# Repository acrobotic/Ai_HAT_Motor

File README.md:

## Ai\_HAT\_Motor

PCB design files (EAGLE) for a Raspberry Pi A+/B+/2/3 HAT carrying a motor
and servo driver ICs (DRV8835 and PCA9685, respectively), as well as a 4-Channel 
ADC (ADS1115). 

## Description

Visit our online shop at:

   * https://acrobotic.com/

Designed by ACROBOTIC Industries.  Please consider buying products from us to 
help fund future Open-Source projects like this! We’ll always put our best 
effort in every project, and release all our design files and code for you to 
use. 

## License

Released under the Creative Commons Attribution, Share-Alike license. Please 
check LICENSE.txt for more information. All text above must be included in any 
redistribution.

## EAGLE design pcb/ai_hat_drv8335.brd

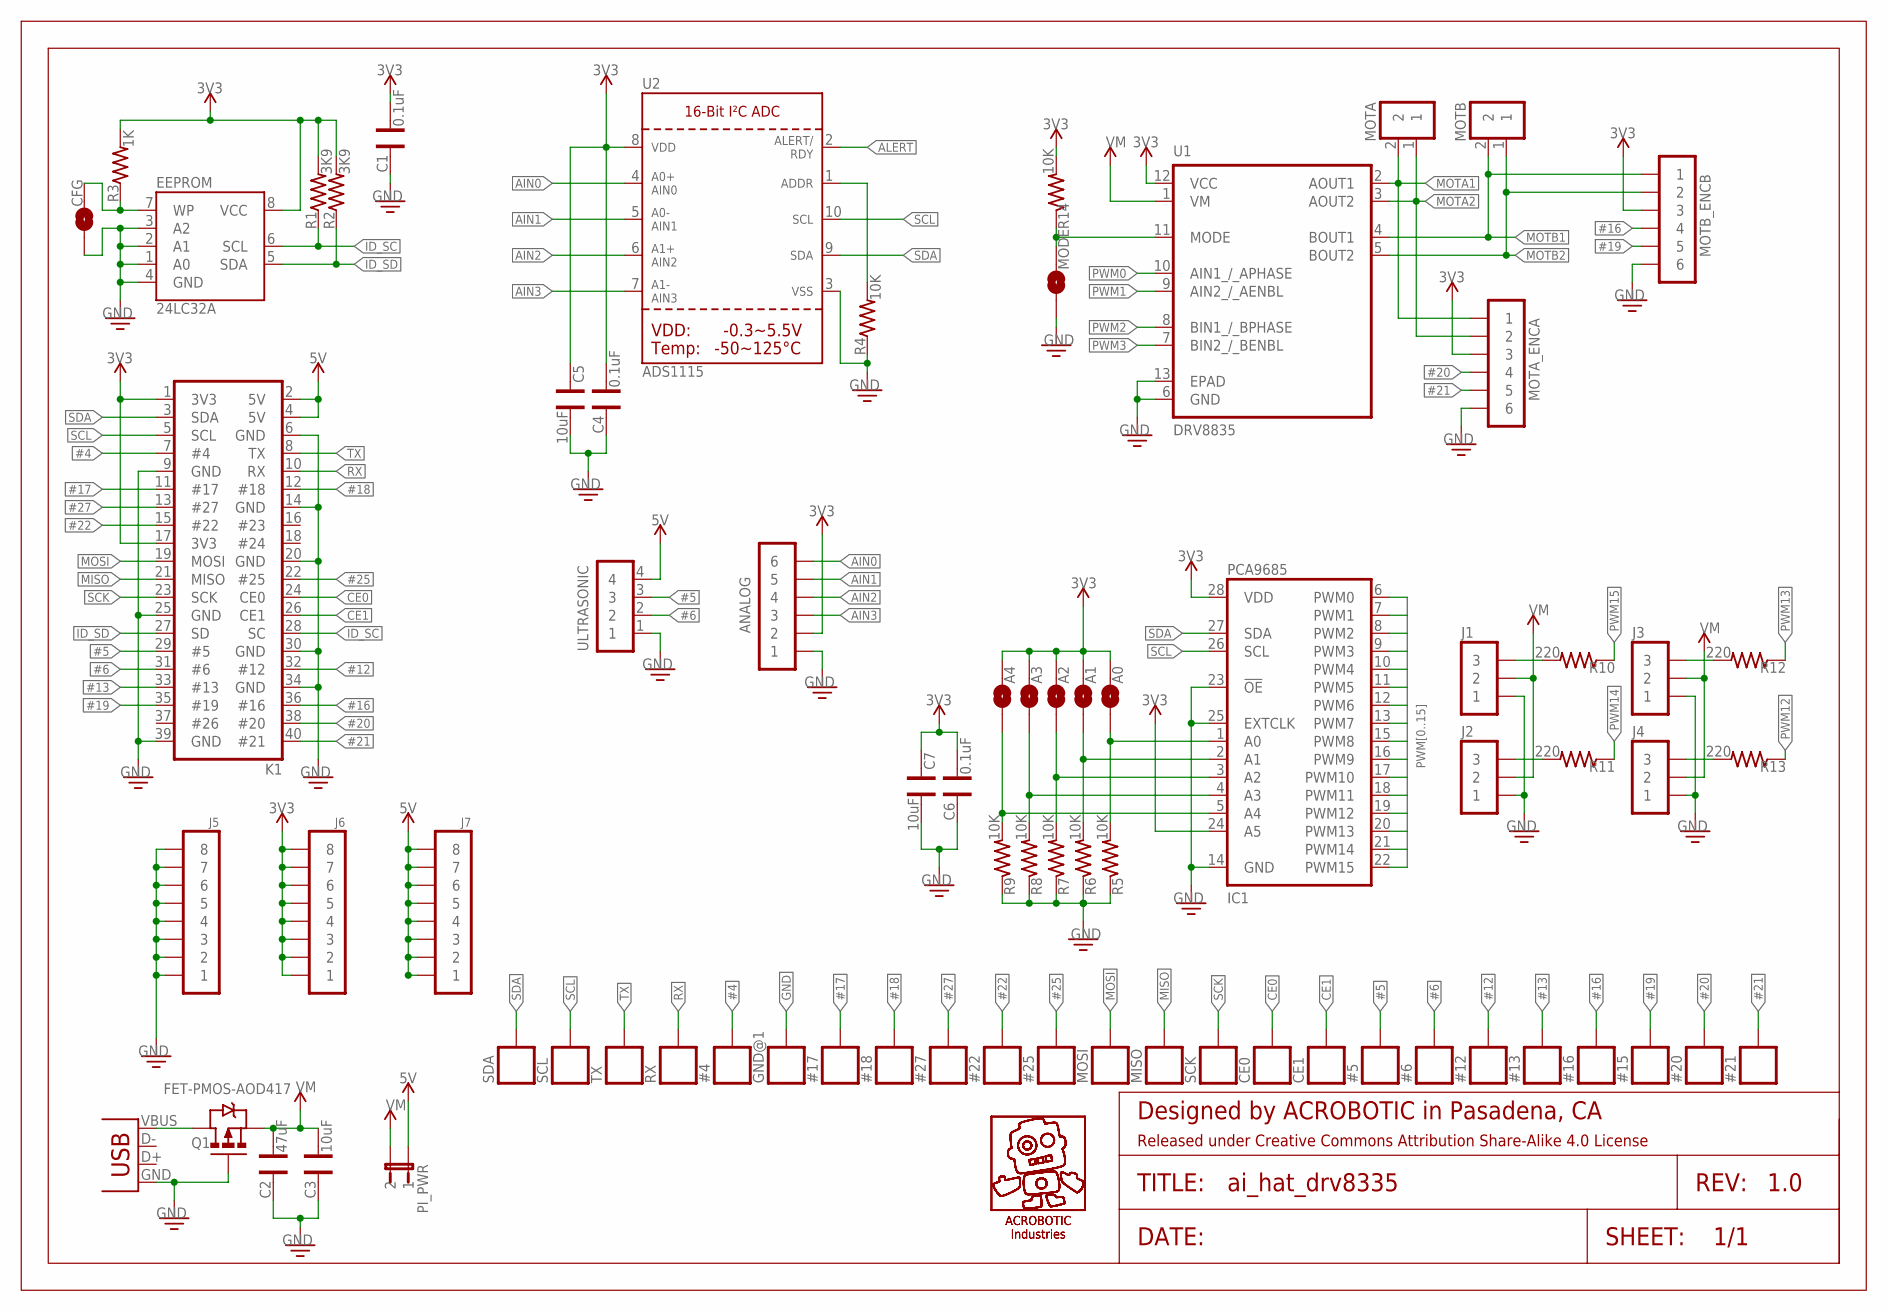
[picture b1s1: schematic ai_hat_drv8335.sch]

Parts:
#4, #5, #6, #12, #13, #15, #16, #17, #18, #20, #21, #22, #25, #27: 1X01-SM
A0, A1, A2, A3, A4: 1X02-SJ-NO
ANALOG: 1X06
C1: 0.1uF; CAP-0603
C2: 47uF; CAP-0603
C3: 10uF; CAP-0603
C4, C6: 0.1uF; CAP-0402
C5, C7: 10uF; CAP-0402
CE0, CE1: 1X01-SM
CFG: 1X02-SJ-NO
EEPROM: 24LC32A; SO08-EIAJ
FRAME1: FRAME-LETTER; CREATIVE-COMMONS
GND@1: 1X01-SM
IC1: PCA9685; TSSOP28
J1, J2, J3, J4: 1X03
J5, J6, J7: 1X08
K1: 2X20-RPI-ALT
MISO: 1X01-SM
MODE: 1X02-SJ-NO
MOSI: 1X01-SM
MOTA: 1X02ST; 1X02-ST
MOTA_ENCA: 1X06
MOTB: 1X02ST; 1X02-ST
MOTB_ENCB: 1X06
PI_PWR: 1X02-PJ; 1X02
PWR_IN: USBMICROB-PTH; USB-MICROB-TH
Q1: FET-PMOS-AOD417; TO-252
R1, R2: 3K9; RES-0603; TOLERANCE 5%
R3: 1K; RES-0603; TOLERANCE 5%
R4: 10K; RES-0402
R5, R6, R7, R8, R9, R14: 10K; RES-0603; TOLERANCE 5%
R10, R11, R12, R13: 220; RES-0603; TOLERANCE 5%
RX: 1X01-SM
SCK: 1X01-SM
SCL: 1X01-SM
SDA: 1X01-SM
TX: 1X01-SM
U1: DRV8835; 12SON
U2: ADS1115; MSOP10
U$9, U$10: AI-LOGOXS; AI-LOGO-XS
ULTRASONIC: 1X04

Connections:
3V3: A0.2, A1.2, A2.2, A3.2, A4.2, ANALOG.2, C1.1, C4.1, C5.2, C6.1, C7.2, EEPROM.8 (VCC), IC1.24 (A5), IC1.28 (VDD), J6.1, J6.2, J6.3, J6.4, J6.5, J6.6, J6.7, J6.8, K1.1 (3V3), K1.17 (3V3), MOTA_ENCA.3, MOTB_ENCB.3, R1.2, R2.2, R3.2, R14.2, U1.12 (VCC), U2.8 (VDD)
5V: J7.1, J7.2, J7.3, J7.4, J7.5, J7.6, J7.7, J7.8, K1.2 (5V), K1.4 (5V), PI_PWR.1, ULTRASONIC.4
#4: #4.1, K1.7 (#4)
#5: #5.1, K1.29 (#5), ULTRASONIC.3
#6: #6.1, K1.31 (#6), ULTRASONIC.2
#12: #12.1, K1.32 (#12)
#13: #13.1, K1.33 (#13)
#16: #16.1, K1.36 (#16), MOTB_ENCB.4
#17: #17.1, K1.11 (#17)
#18: #18.1, K1.12 (#18)
#19: #15.1, K1.35 (#19), MOTB_ENCB.5
#20: #20.1, K1.38 (#20), MOTA_ENCA.4
#21: #21.1, K1.40 (#21), MOTA_ENCA.5
#22: #22.1, K1.15 (#22)
#25: #25.1, K1.22 (#25)
#27: #27.1, K1.13 (#27)
A0: A0.1, IC1.1 (A0), R5.2
A1: A1.1, IC1.2 (A1), R6.2
A2: A2.1, IC1.3 (A2), R7.2
A3: A3.1, IC1.4 (A3), R8.2
A4: A4.1, IC1.5 (A4), R9.2
AIN0: ANALOG.6, U2.4 (AIN0)
AIN1: ANALOG.5, U2.5 (AIN1)
AIN2: ANALOG.4, U2.6 (AIN2)
AIN3: ANALOG.3, U2.7 (AIN3)
ALERT: U2.2 (ALERT/RDY)
CE0: CE0.1, K1.24 (CE0)
CE1: CE1.1, K1.26 (CE1)
GND: ANALOG.1, C1.2, C2.2, C3.2, C4.2, C5.1, C6.2, C7.1, CFG.1, EEPROM.1 (A0), EEPROM.2 (A1), EEPROM.3 (A2), EEPROM.4 (GND), GND@1.1, IC1.14 (GND), IC1.23 (!OE), IC1.25 (EXTCLK), J1.1, J2.1, J3.1, J4.1, J5.1, J5.2, J5.3, J5.4, J5.5, J5.6, J5.7, J5.8, K1.6 (GND), K1.9 (GND), K1.14 (GND), K1.20 (GND), K1.25 (GND), K1.30 (GND), K1.34 (GND), K1.39 (GND), MODE.1, MOTA_ENCA.6, MOTB_ENCB.6, PWR_IN.GND, Q1.G, R4.1, R5.1, R6.1, R7.1, R8.1, R9.1, U1.6 (GND), U1.13 (EPAD), U2.3 (VSS), ULTRASONIC.1
ID_SC: EEPROM.6 (SCL), K1.28 (SC), R1.1
ID_SD: EEPROM.5 (SDA), K1.27 (SD), R2.1
MISO: K1.21 (MISO), MISO.1
MOSI: K1.19 (MOSI), MOSI.1
MOTA1: MOTA.2, MOTA_ENCA.1, U1.2 (AOUT1)
MOTA2: MOTA.1, MOTA_ENCA.2, U1.3 (AOUT2)
MOTB1: MOTB.2, MOTB_ENCB.1, U1.4 (BOUT1)
MOTB2: MOTB.1, MOTB_ENCB.2, U1.5 (BOUT2)
unnamed: R4.2, U2.1 (ADDR)
unnamed: MODE.2, R14.1, U1.11 (MODE)
unnamed: CFG.2, EEPROM.7 (WP), R3.1
unnamed: PWR_IN.VBUS, Q1.D
unnamed: J1.3, R10.2
unnamed: J4.3, R13.2
unnamed: J3.3, R12.2
unnamed: J2.3, R11.2
PWM0: IC1.6 (PWM0), U1.10 (AIN1_/_APHASE)
PWM1: IC1.7 (PWM1), U1.9 (AIN2_/_AENBL)
PWM2: IC1.8 (PWM2), U1.8 (BIN1_/_BPHASE)
PWM3: IC1.9 (PWM3), U1.7 (BIN2_/_BENBL)
PWM4: IC1.10 (PWM4)
PWM5: IC1.11 (PWM5)
PWM6: IC1.12 (PWM6)
PWM7: IC1.13 (PWM7)
PWM8: IC1.15 (PWM8)
PWM9: IC1.16 (PWM9)
PWM10: IC1.17 (PWM10)
PWM11: IC1.18 (PWM11)
PWM12: IC1.19 (PWM12), R13.1
PWM13: IC1.20 (PWM13), R12.1
PWM14: IC1.21 (PWM14), R11.1
PWM15: IC1.22 (PWM15), R10.1
RX: K1.10 (RX), RX.1
SCK: K1.23 (SCK), SCK.1
SCL: IC1.26 (SCL), K1.5 (SCL), SCL.1, U2.10 (SCL)
SDA: IC1.27 (SDA), K1.3 (SDA), SDA.1, U2.9 (SDA)
TX: K1.8 (TX), TX.1
VM: C2.1, C3.1, J1.2, J2.2, J3.2, J4.2, PI_PWR.2, Q1.S, U1.1 (VM)

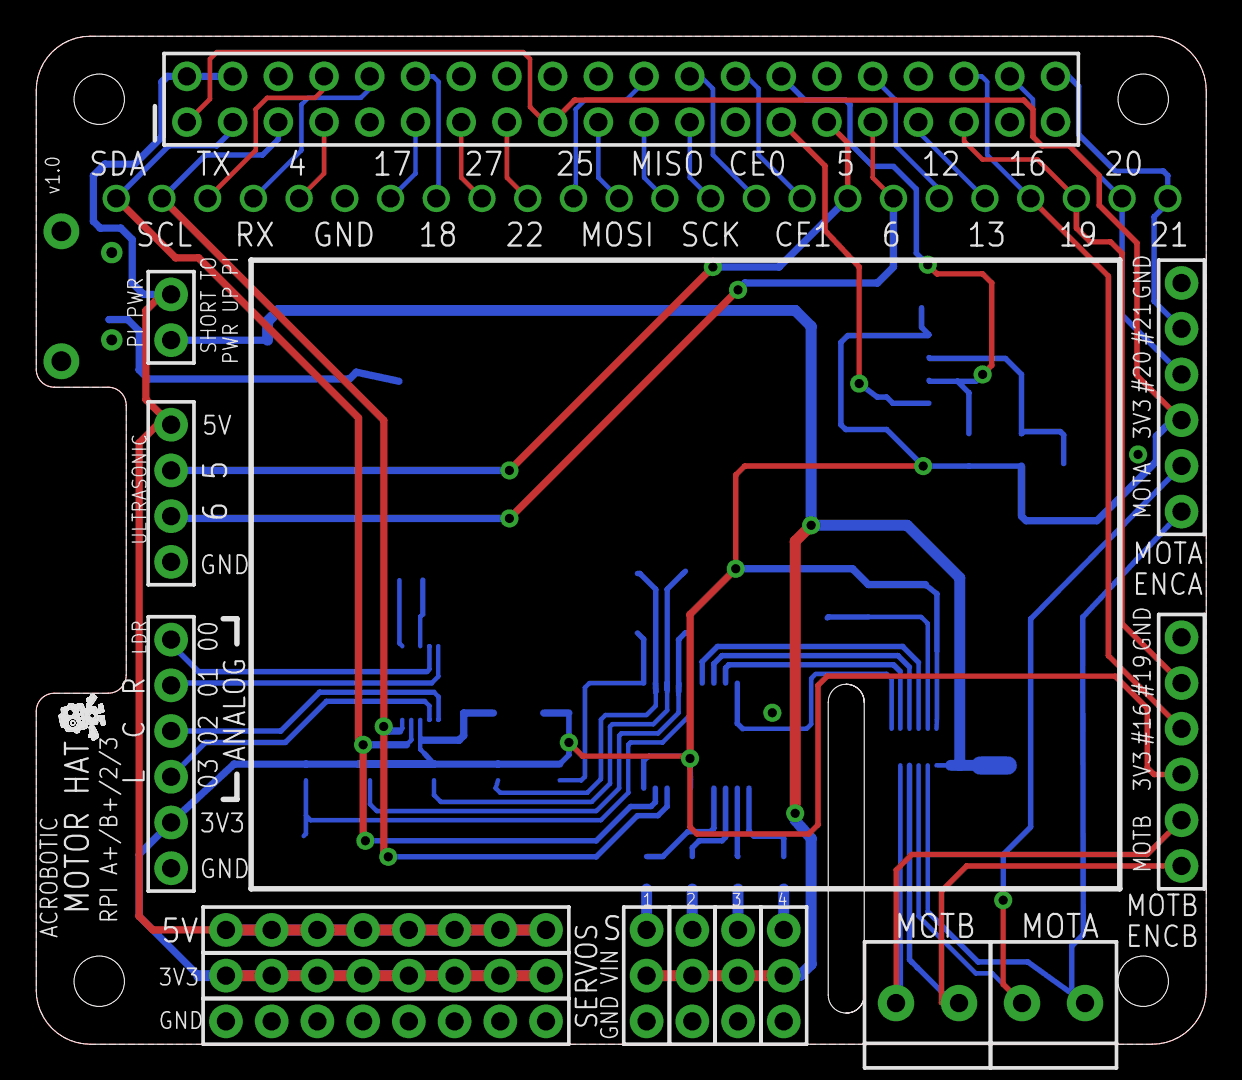
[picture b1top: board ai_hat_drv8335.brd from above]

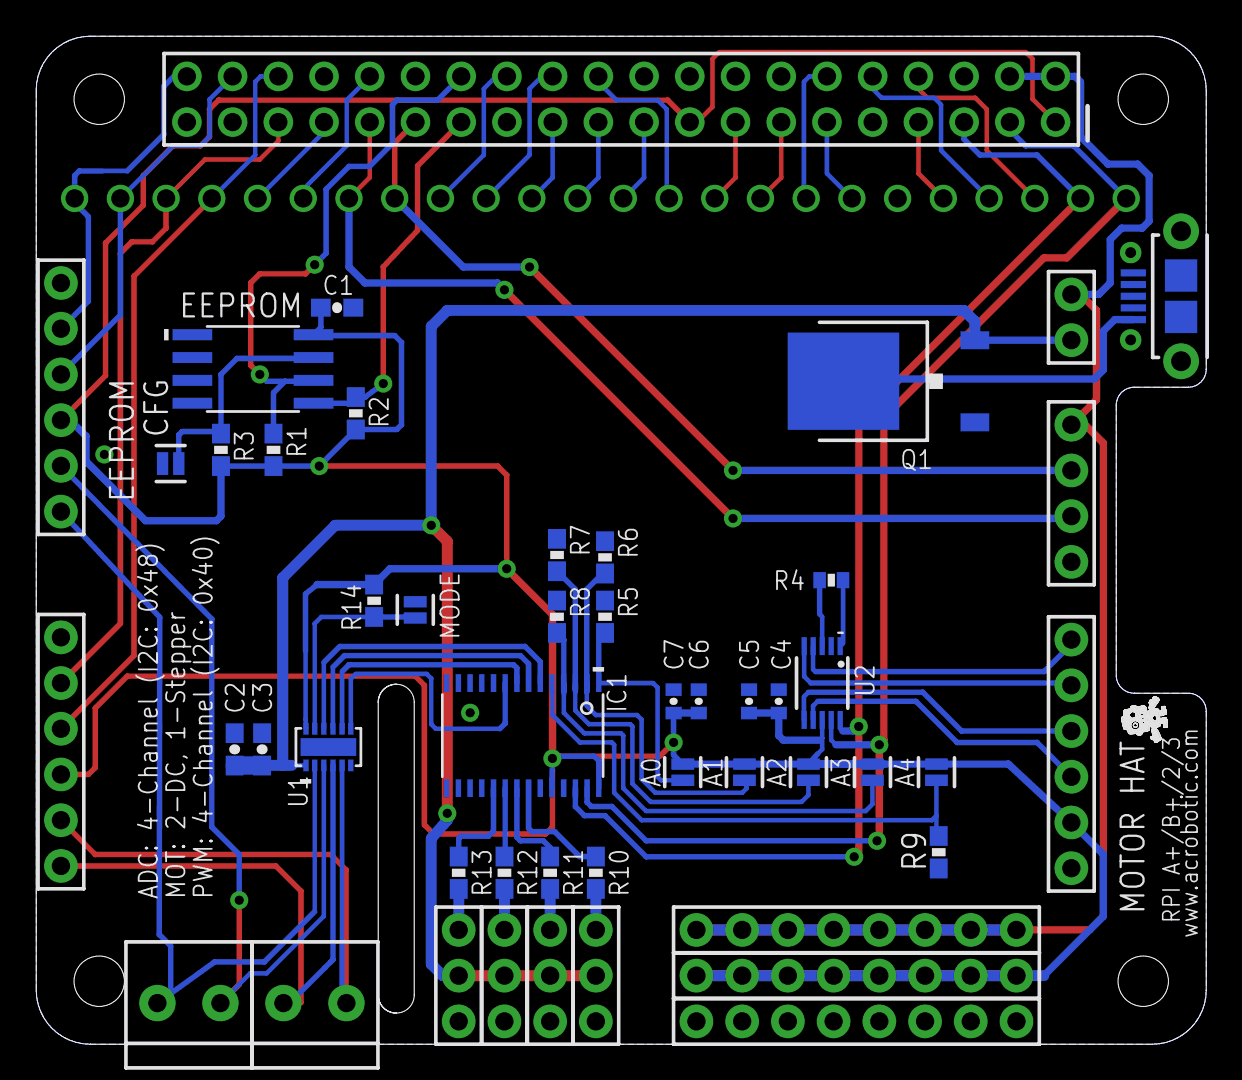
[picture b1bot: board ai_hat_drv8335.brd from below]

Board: 2 copper layers, 65.0 x 56.0 mm, 76 parts (35 on the bottom side), 58 nets.

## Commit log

2016-05-11 adding schematic .pdf
2016-07-21 updating

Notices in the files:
parts and their libraries:
Ai_Miscellany: Attribution Share-Alike 4.0 License
Ai_Miscellany: https://creativecommons.org/licenses/by-sa/4.0
Ai_Miscellany: Released under Creative Commons Attribution Share-Alike 4.0 License
